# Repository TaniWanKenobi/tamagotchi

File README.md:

<p align="center">

</p>

<br />

<div align="center">
  
</div>

<h3 align="center">Tamagotchi</h3>

<p align="center">
  A custom PCB-based Tamagotchi virtual pet built with the XIAO-ESP32-C6!
</p>

<details>
  <summary>Table of Contents</summary>
  <ol>
    <li>
      <a href="#about-the-project">About The Project</a>
      <ul>
        <li><a href="#built-with">Built With</a></li>
        <li><a href="#pcb-design">PCB Design</a></li>
        <li><a href="#3d-model">3D Model</a></li>
        <li><a href="#bom">BOM</a></li>
      </ul>
    </li>
    <li><a href="#contact">Contact</a></li>
  </ol>
</details>

## About The Project

<div align="center">
  
</div>

A custom PCB-based Tamagotchi virtual pet built with the XIAO-ESP32-C6 microcontroller, featuring a 0.96" OLED display, three buttons, and a buzzer.

I made the project to have my own completely customizable tamagatchi! I also want you to customize yours however you want - check my [tutorial](/tutorial.md) for instructions! 

To use this, simply flash the xiao with the firmware in the repo! Here is an assembly diagram:

### PCB Design

Here is my PCB:

Here is the schematic used to make the PCB:

### 3D Model

Here is the [Onshape link](https://cad.onshape.com/documents/fa5791d8e7f345b436054923/w/ad8e09905eb572b0a8a40e9d/e/e81f06aa82a76dd04f8e6832?renderMode=0&uiState=699271dcf72b31b660e722c3)!

### BOM

| Component | Qty | Price | Tax (6.7%) | Total | Link |
|-----------|-----|-------|------------|-------|------|
| XIAO-ESP32-C6 | 1 | $5.20 | $0.35 | $5.55 | [Seeed Studio](https://www.seeedstudio.com/Seeed-Studio-XIAO-ESP32C6-p-5884.html) |
| Seeed Studio Shipping | 1 | $6.69 | $0.45 | $7.14 | — |
| 0.96" OLED Display | 1 | $2.15 | $0.14 | $2.29 | [LCSC](https://www.lcsc.com/product-detail/C5248080.html) |
| Tactile Button | 3 | $0.50 | $0.03 | $0.53 | [LCSC](https://www.lcsc.com/product-detail/C2888493.html) |
| Buzzer | 1 | $0.54 | $0.04 | $0.58 | [LCSC](https://www.lcsc.com/product-detail/C49246964.html) |
| Male Pin Headers (20 pcs) | 1 | $0.59 | $0.04 | $0.63 | [LCSC](https://www.lcsc.com/product-detail/C49261205.html) |
| LCSC Shipping | 1 | $14.73 | $0.99 | $15.72 | — |
| JLCPCB PCB | 1 | $5.40 | $0.36 | $5.76 | [JLCPCB](https://jlcpcb.com/) |
| JLCPCB Shipping | 1 | $3.30 | $0.22 | $3.52 | — |
| M3 8mm Screws | 1 | $2.28 | $0.15 | $2.43 | [AliExpress](https://www.aliexpress.us/item/3256809831708799.html) |
| Brass Threaded Inserts | 1 | $5.79 | $0.39 | $6.18 | [AliExpress](https://www.aliexpress.us/item/3256806286648221.html) |
| | | | | | |
| **Total** | | **$47.17** | **$3.16** | **$50.33** | |

## Contact

Tanishq Goyal - @Tanuki - [tanishqgoyal590@gmail.com](mailto:tanishqgoyal590@gmail.com)

<p align="right">(<a href="#readme-top">back to top</a>)</p>

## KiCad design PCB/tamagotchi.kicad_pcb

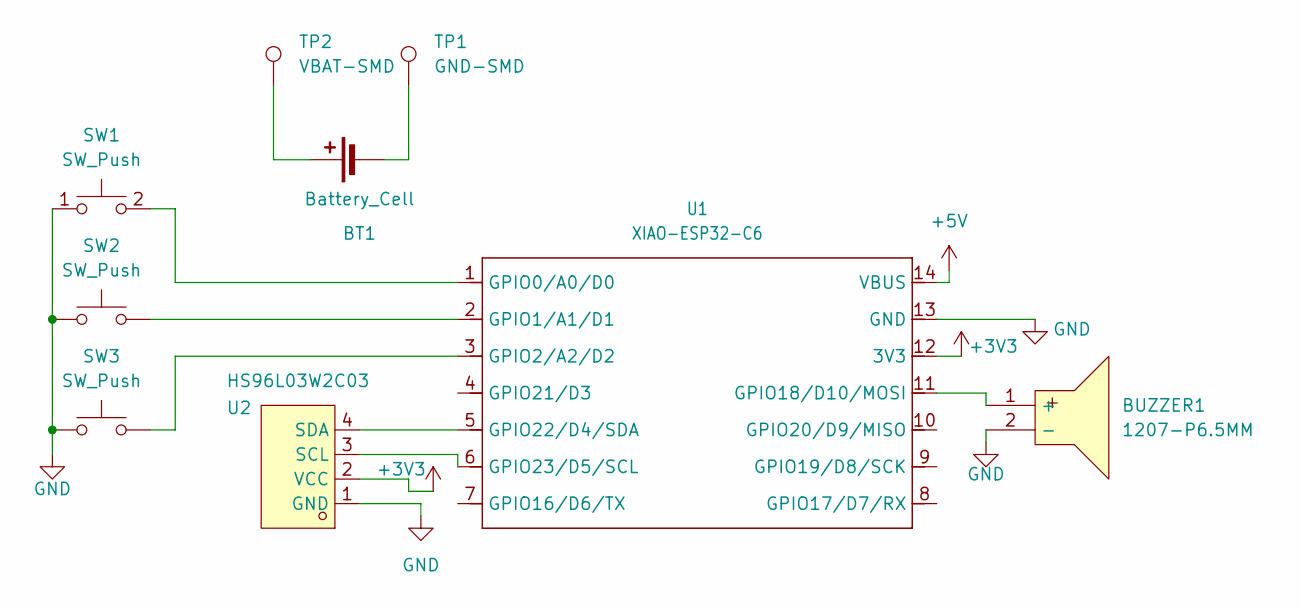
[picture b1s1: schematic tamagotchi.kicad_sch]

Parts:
BT1: Battery_Cell; PinHeader_1x02_P2.54mm_Vertical
BUZZER1: 1207-P6.5MM; BUZ-TH_BD12.5-P6.50-D1.4; LCSC Part C49246964
SW1, SW2, SW3: SW_Push; SW-TH_4P-L4.5-W4.5-P3.00-LS4.8
TP1: GND-SMD; TestPoint_Pad_D2.0mm
TP2: VBAT-SMD; TestPoint_Pad_D2.0mm
U1: XIAO-ESP32-C6; XIAO-ESP32C6-DIP
U2: HS96L03W2C03; OLED-TH_L27.8-W27.2-P2.54_C9900033791; LCSC Part C5248080

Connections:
+3V3: U1.12 (3V3), U2.2 (VCC)
+5V: U1.14 (VBUS)
GND: BUZZER1.2 (-), SW1.1, SW2.1, SW3.1, U1.13 (GND), U2.1 (GND)
unnamed: BT1.1 (+), TP2.1 (1_1)
unnamed: BT1.2 (-), TP1.1 (1_1)
unnamed: BUZZER1.1 (+), U1.11 (GPIO18/D10/MOSI)
unnamed: SW1.2, U1.1 (GPIO0/A0/D0)
unnamed: SW2.2, U1.2 (GPIO1/A1/D1)
unnamed: SW3.2, U1.3 (GPIO2/A2/D2)
unnamed: U1.5 (GPIO22/D4/SDA), U2.4 (SDA)
unnamed: U1.6 (GPIO23/D5/SCL), U2.3 (SCL)

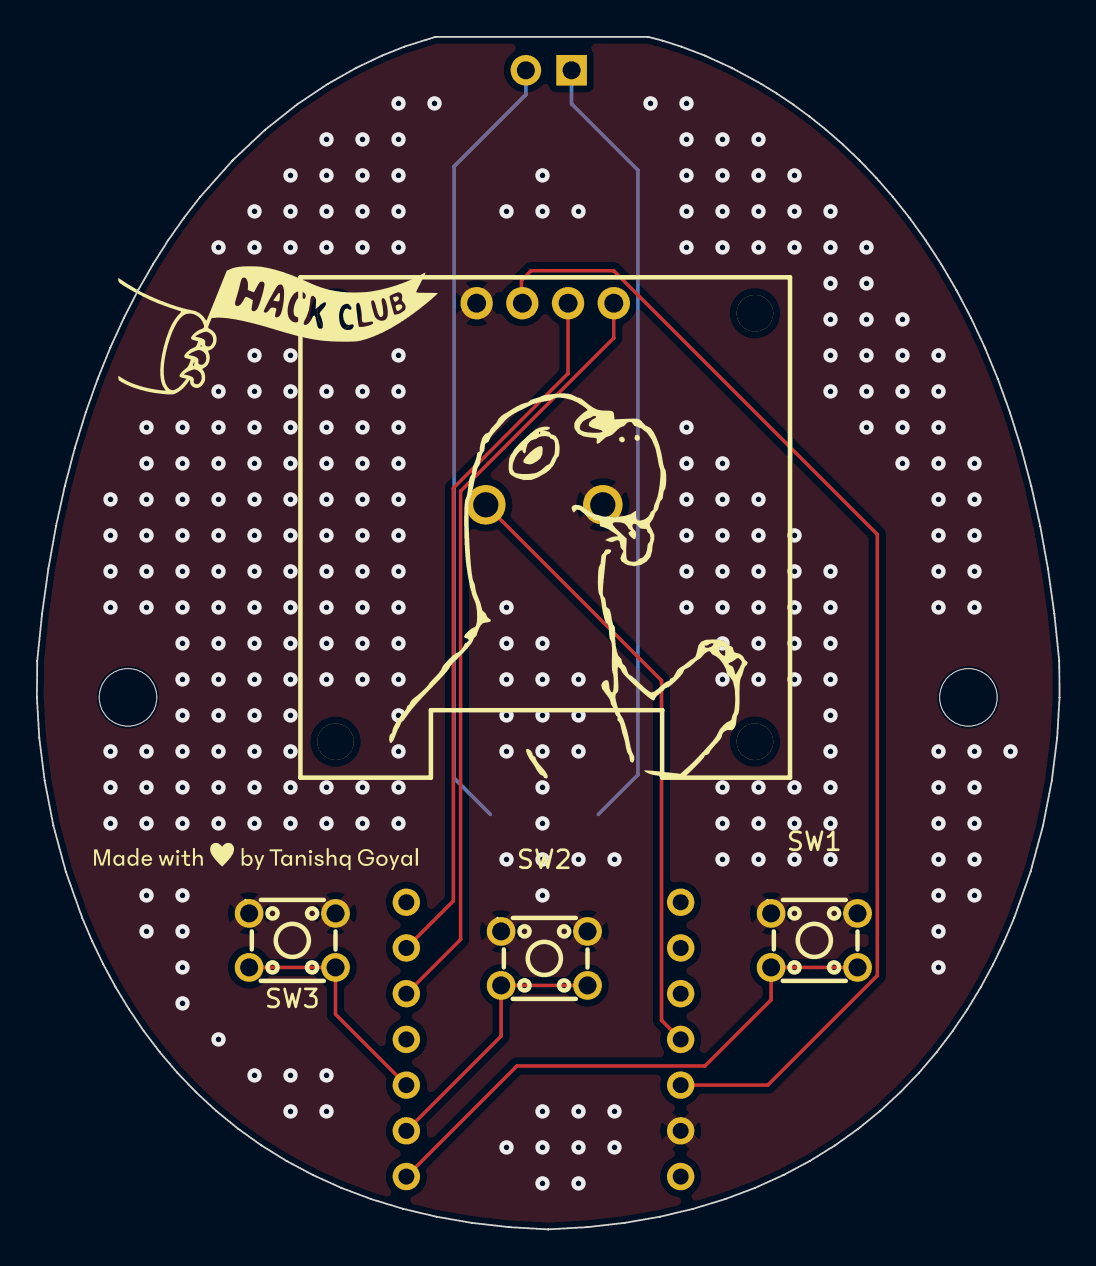
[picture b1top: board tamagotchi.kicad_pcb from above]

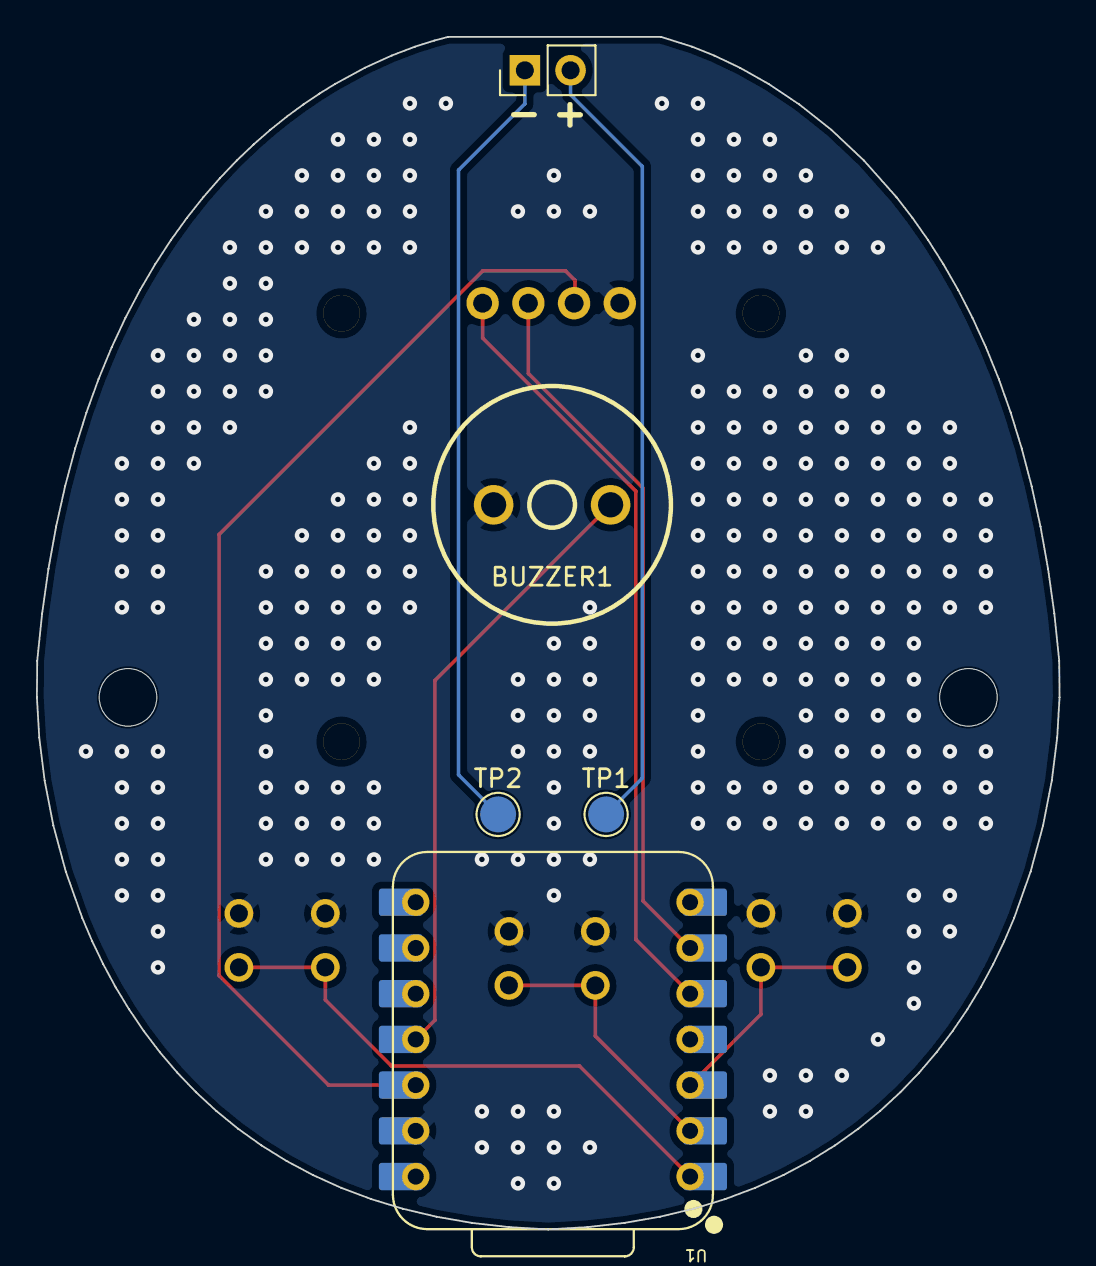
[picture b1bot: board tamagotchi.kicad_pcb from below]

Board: 2 copper layers, 56.8 x 66.2 mm, 9 parts (5 on the bottom side), 10 nets.

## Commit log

2026-02-12 Enhance PCB tutorial with detailed steps and images
    Expanded tutorial with detailed steps for creating a PCB using KiCad, including wiring, design rules check, and GitHub integration.
2026-02-14 made tutorial
2026-02-16 base file uploades
2026-02-16 Add BOM to readme
2026-02-16 Add .csv BOM
2026-02-16 Add hyperlink to tutorial in readme
2026-02-16 Replace Xiao git cdn with slack cdn
2026-02-16 Add firmware tutorial v1
2026-02-16 Pretty firmweare
2026-02-16 Add detailed KiCad installation instructions and shortcuts to tutorial
2026-02-16 Remove redundant details section from KiCad installation instructions
2026-02-17 Fix BOM.csv formatting and remove empty line
2026-02-17 Fix typo in OLED Display component name
2026-02-18 Add Tamagotchi game implementation with OLED display and button controls
    - Implemented pet model with hunger, happiness, energy, and age attributes.
    - Created state machine for different screens: main, feed, play, and sleep.
    - Added sprite graphics for pet states (happy, sad, neutral, sleep).
    - Developed functions for updating pet status, handling button inputs, and rendering display.
    - Integrated buzzer feedback for button presses.
    - Initialized pet attributes in setup and managed game loop in main loop.
2026-02-18 Update README with usage intrsuctions
2026-02-18 Refactor firmware tutorial for clarity and conciseness
2026-03-13 Update Gerber files for PCB design
2026-04-06 Fixing schematic
2026-04-06 Remove outdated test documentation and add image to tutorial for clarity
2026-04-06 Refactor code structure for improved readability and maintainability
2026-04-06 Add section for Button Footprint Mismatch in PCB tutorial
2026-04-07 Added Post-Mortem
2026-04-07 Correct capitalization in note section of tutorial for consistency
2026-04-07 Update KiCad getting started link
2026-04-07 remove repeat note
2026-04-07 fix shipping instrutions
2026-04-09 Enhance tutorial with additional MCU options and design tips
2026-04-09 Add link to Onshape tutorial in PCB export section
2026-04-11 Correct MCU reference from C6 to C3 in tutorial
    Updated references from XIAO-ESP32-C6 to XIAO-ESP32-C3 for accuracy in the tutorial.
2026-04-12 Update BOM.csv with new item details and format
2026-04-21 FInal
2026-04-21 Revise tutorial structure and content for clarity and completeness
2026-06-04 Add voltage information, as well as useful diagrams
